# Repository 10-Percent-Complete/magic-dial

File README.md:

# Magic Dial

## Crates for custom PCB
| Name    | Description          | Crate                              |
| ------- | -------------------- | ---------------------------------- |
| HX711   | Strain Gauge IC      | https://crates.io/crates/hx711     |
| GC9A01  | LCD Screen           | https://crates.io/crates/gc9a01-rs |
| MT6701  | Hall Encoder         | https://crates.io/crates/mt6701    |
| TMC6300 | Motor Driver         | N/A                                |
| INA420  | Inline Phase Current | N/A                                |

## Info about devlepment board
| Name                        | URL                                                                         |
| --------------------------- | --------------------------------------------------------------------------- |
| Sparkfun Board              | https://docs.sparkfun.com/SparkFun_IoT_Brushless_Motor_Driver/introduction/ |
| TMC6300 Motor Driver        |                                                                             |
| TMAG5273 Hall Encoder       |                                                                             |
| INA420 Inline Phase Current |                                                                             |
| MCP6021 Low-side Op Amp     |                                                                             |
| WS2812 RGB LED              | https://crates.io/crates/ws2812-spi                                         |

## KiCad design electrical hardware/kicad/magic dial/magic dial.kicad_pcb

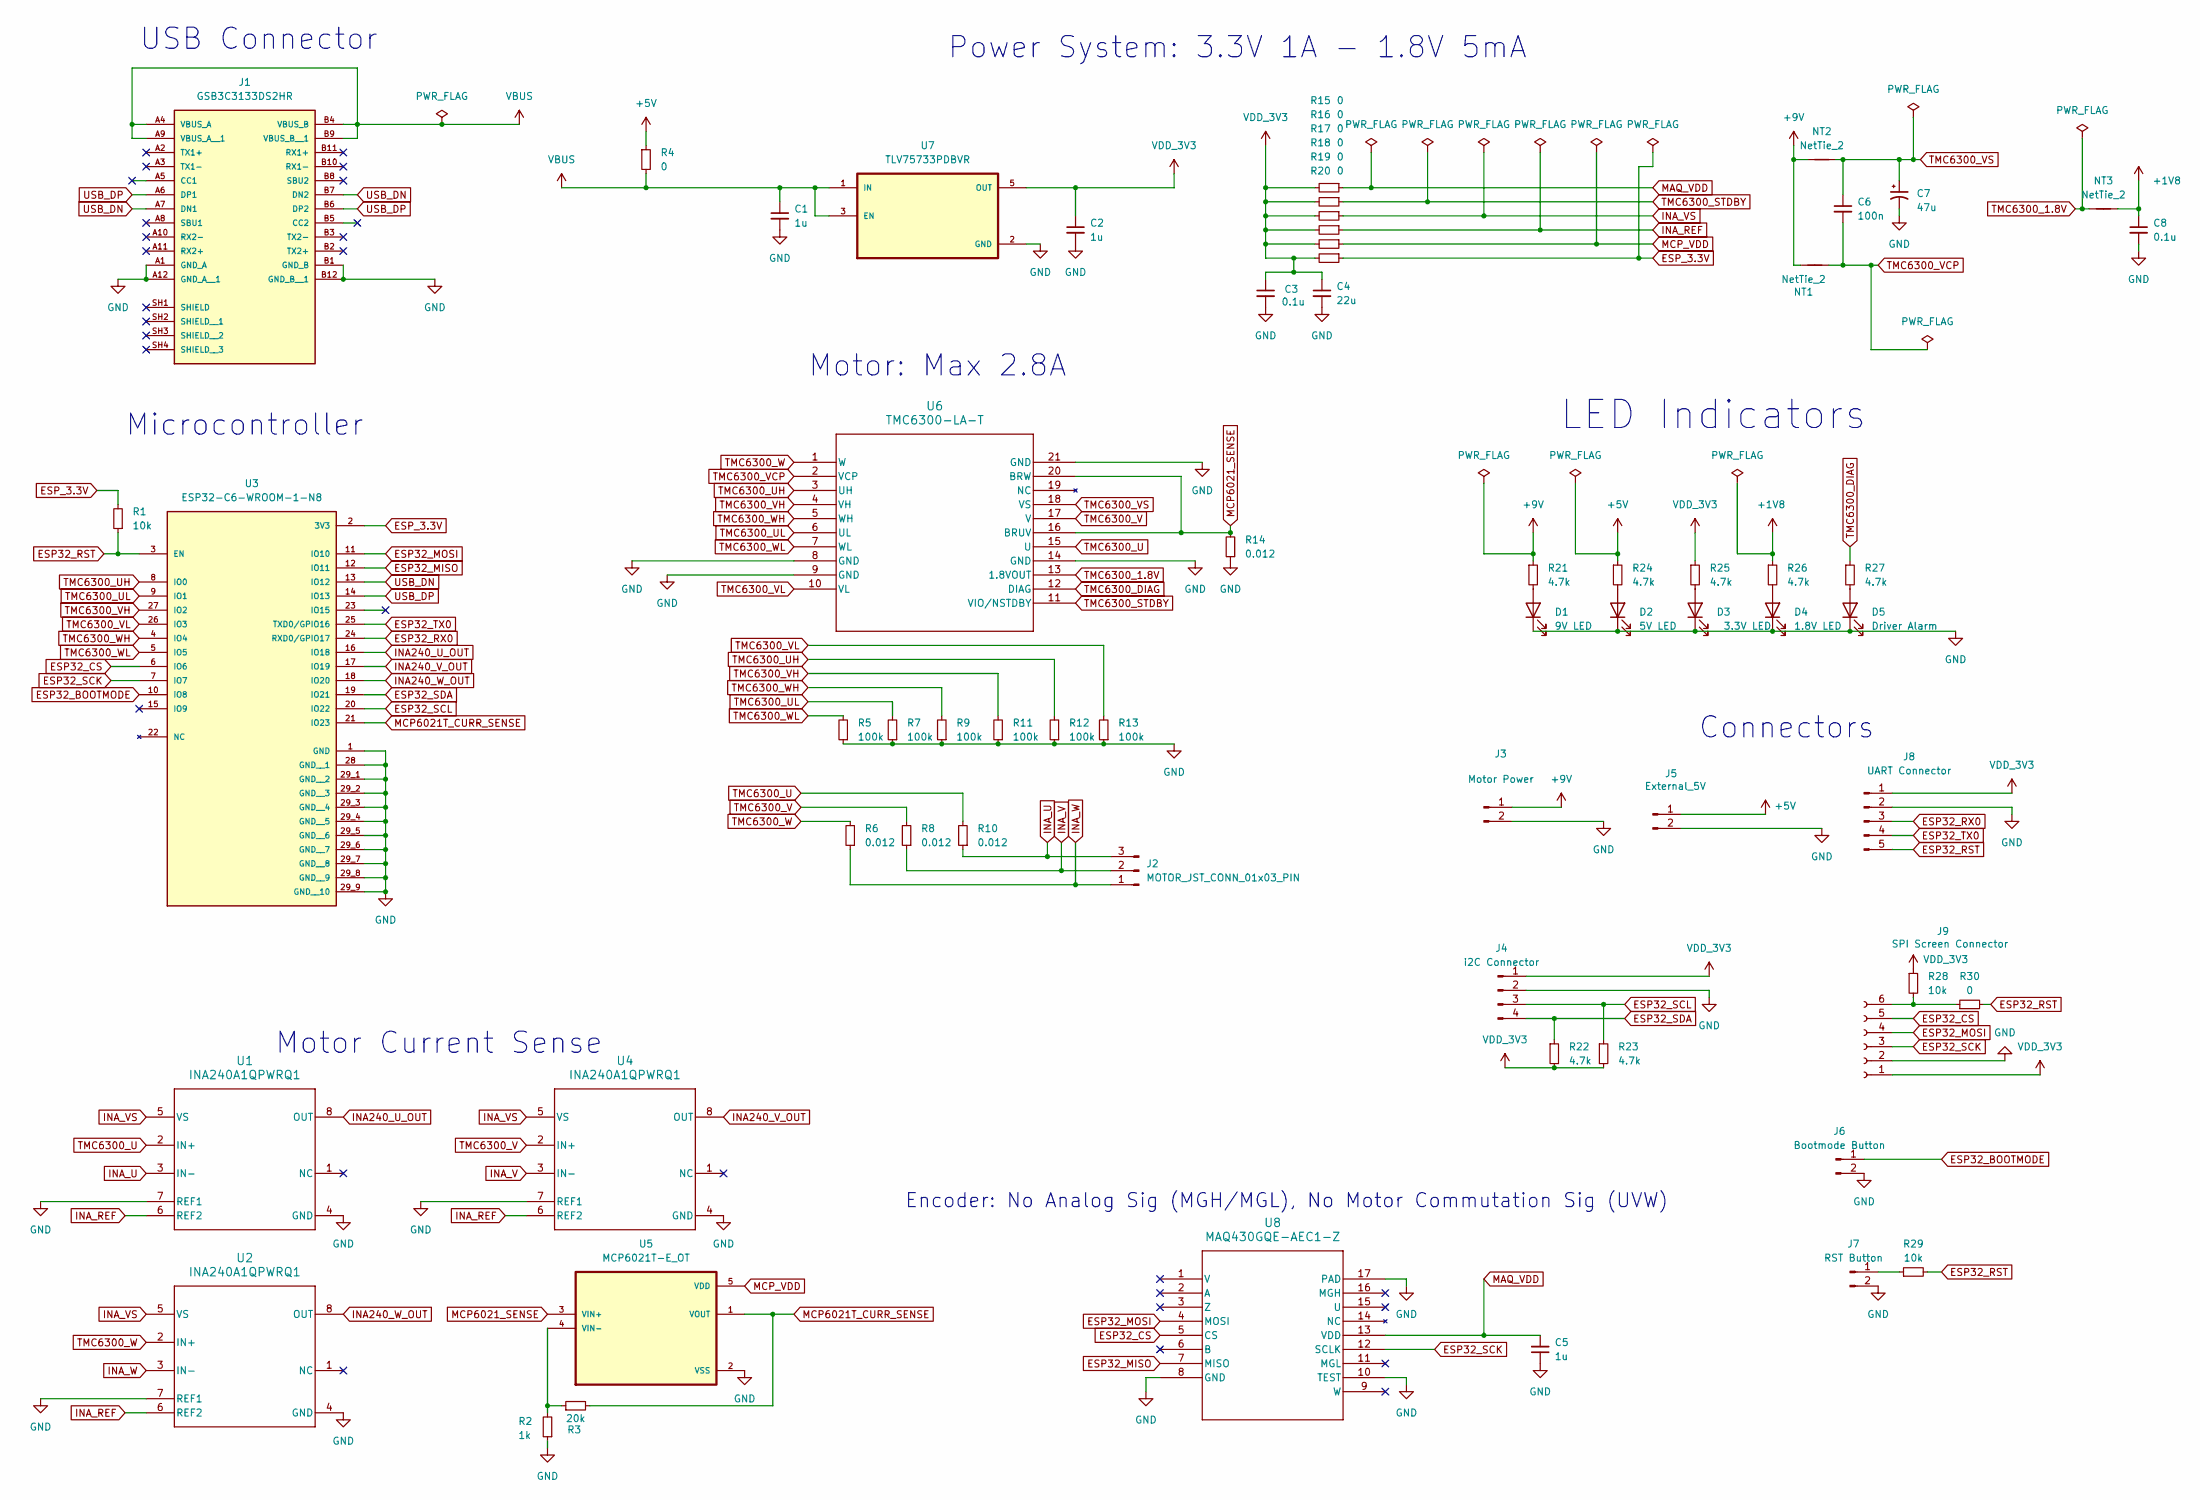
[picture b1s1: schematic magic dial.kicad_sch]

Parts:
C1, C2, C5: 1u; C_1206_3216Metric
C3, C8: 0.1u; C_1206_3216Metric
C4: 22u; C_1206_3216Metric
C6: 100n; C_1206_3216Metric
C7: 47u; C_1206_3216Metric
D1: 9V LED; LED_1206_3216Metric
D2: 5V LED; LED_1206_3216Metric
D3: 3.3V LED; LED_1206_3216Metric
D4: 1.8V LED; LED_1206_3216Metric
D5: Driver Alarm; LED_1206_3216Metric
J1: GSB3C3133DS2HR; AMPHENOL_GSB3C3133DS2HR; PARTREV AX1
J2: MOTOR_JST_CONN_01x03_PIN; JST_GH_SM03B-GHS-TB_1x03-1MP_P1.25mm_Horizontal
J3: Motor Power; PinHeader_1x02_P2.54mm_Vertical
J4: i2C Connector; PinHeader_1x04_P2.54mm_Vertical
J5: External_5V; PinHeader_1x02_P2.54mm_Vertical
J6: Bootmode Button; PinHeader_1x02_P2.54mm_Vertical
J7: RST Button; PinHeader_1x02_P2.54mm_Vertical
J8: UART Connector; PinHeader_1x05_P2.54mm_Vertical
J9: SPI Screen Connector; PinHeader_1x06_P2.54mm_Vertical
NT1, NT2, NT3: NetTie_2; NetTie-2_SMD_Pad0.5mm
R1, R28, R29: 10k; R_1206_3216Metric
R2: 1k; R_1206_3216Metric
R3: 20k; R_1206_3216Metric
R4, R15, R16, R17, R18, R19, R20, R30: 0; R_1206_3216Metric
R5, R7, R9, R11, R12, R13: 100k; R_1206_3216Metric
R6, R8, R10, R14: 0.012; R_1206_3216Metric
R21, R22, R23, R24, R25, R26, R27: 4.7k; R_1206_3216Metric
U1, U2, U4: INA240A1QPWRQ1; PW0008A_M
U3: ESP32-C6-WROOM-1-N8; XCVR_ESP32-C6-WROOM-1-N8; PARTREV 1.0
U5: MCP6021T-E_OT; SOT95P270X145-5N
U6: TMC6300-LA-T; 21-100586_K2033&plus_1C_ADI-M
U7: TLV75733PDBVR; SOT95P280X145-5N
U8: MAQ430GQE-AEC1-Z; QFN-16_MAQ430-M

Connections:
+1V8: C8.1, NT3.2, R26.1
+5V: J5.1, R4.1, R24.1
+9V: J3.1, NT1.1, NT2.1, R21.1
ESP32_BOOTMODE: J6.1, U3.10 (IO8)
ESP32_CS: J9.5, U3.6 (IO6), U8.5 (CS)
ESP32_MISO: U3.12 (IO11), U8.7 (MISO)
ESP32_MOSI: J9.4, U3.11 (IO10), U8.4 (MOSI)
ESP32_RST: J8.5, R1.1, R29.2, R30.2, U3.3 (EN)
ESP32_RX0: J8.3, U3.24 (RXD0/GPIO17)
ESP32_SCK: J9.3, U3.7 (IO7), U8.12 (SCLK)
ESP32_SCL: J4.3, R23.1, U3.20 (IO22)
ESP32_SDA: J4.4, R22.1, U3.19 (IO21)
ESP32_TX0: J8.4, U3.25 (TXD0/GPIO16)
ESP_3.3V: R1.2, R20.1, U3.2 (3V3)
GND: C1.2, C2.2, C3.2, C4.2, C5.1, C7.2, C8.2, D1.1 (K), D2.1 (K), D3.1 (K), D4.1 (K), D5.1 (K), J1.A1 (GND_A), J1.A12 (GND_A__1), J1.B1 (GND_B), J1.B12 (GND_B__1), J3.2, J4.2, J5.2, J6.2, J7.2, J8.2, J9.2, R2.1, R5.1, R7.1, R9.1, R11.1, R12.1, R13.1, R14.1, U1.4 (GND), U1.7 (REF1), U2.4 (GND), U2.7 (REF1), U3.1 (GND), U3.28 (GND__1), U3.29_1 (GND__2), U3.29_2 (GND__3), U3.29_3 (GND__4), U3.29_4 (GND__5), U3.29_5 (GND__6), U3.29_6 (GND__7), U3.29_7 (GND__8), U3.29_8 (GND__9), U3.29_9 (GND__10), U4.4 (GND), U4.7 (REF1), U5.2 (VSS), U6.8 (GND), U6.9 (GND), U6.14 (GND), U6.21 (GND), U7.2 (GND), U8.8 (GND), U8.10 (TEST), U8.17 (PAD)
INA240_U_OUT: U1.8 (OUT), U3.16 (IO18)
INA240_V_OUT: U3.17 (IO19), U4.8 (OUT)
INA240_W_OUT: U2.8 (OUT), U3.18 (IO20)
INA_REF: R18.1, U1.6 (REF2), U2.6 (REF2), U4.6 (REF2)
INA_U: J2.3, R10.1, U1.3 (IN-)
INA_V: J2.2, R8.1, U4.3 (IN-)
INA_VS: R17.1, U1.5 (VS), U2.5 (VS), U4.5 (VS)
INA_W: J2.1, R6.1, U2.3 (IN-)
MAQ_VDD: C5.2, R15.1, U8.13 (VDD)
MCP6021T_CURR_SENSE: R3.2, U3.21 (IO23), U5.1 (VOUT)
MCP6021_SENSE: R14.2, U5.3 (VIN+), U6.16 (BRUV), U6.20 (BRW)
MCP_VDD: R19.1, U5.5 (VDD)
unnamed: D1.2 (A), R21.2
unnamed: D2.2 (A), R24.2
unnamed: D3.2 (A), R25.2
unnamed: D4.2 (A), R26.2
unnamed: D5.2 (A), R27.2
unnamed: J7.1, R29.1
unnamed: J9.6, R28.2, R30.1
unnamed: R2.2, R3.1, U5.4 (VIN-)
TMC6300_1.8V: NT3.1, U6.13 (1.8VOUT)
TMC6300_DIAG: R27.1, U6.12 (DIAG)
TMC6300_STDBY: R16.1, U6.11 (VIO/NSTDBY)
TMC6300_U: R10.2, U1.2 (IN+), U6.15 (U)
TMC6300_UH: R12.2, U3.8 (IO0), U6.3 (UH)
TMC6300_UL: R7.2, U3.9 (IO1), U6.6 (UL)
TMC6300_V: R8.2, U4.2 (IN+), U6.17 (V)
TMC6300_VCP: C6.2, NT1.2, U6.2 (VCP)
TMC6300_VH: R11.2, U3.27 (IO2), U6.4 (VH)
TMC6300_VL: R13.2, U3.26 (IO3), U6.10 (VL)
TMC6300_VS: C6.1, C7.1, NT2.2, U6.18 (VS)
TMC6300_W: R6.2, U2.2 (IN+), U6.1 (W)
TMC6300_WH: R9.2, U3.4 (IO4), U6.5 (WH)
TMC6300_WL: R5.2, U3.5 (IO5), U6.7 (WL)
USB_DN: J1.A7 (DN1), J1.B7 (DN2), U3.13 (IO12)
USB_DP: J1.A6 (DP1), J1.B6 (DP2), U3.14 (IO13)
VBUS: C1.1, J1.A4 (VBUS_A), J1.A9 (VBUS_A__1), J1.B4 (VBUS_B), J1.B9 (VBUS_B__1), R4.2, U7.1 (IN), U7.3 (EN)
VDD_3V3: C2.1, C3.1, C4.1, J4.1, J8.1, J9.1, R15.2, R16.2, R17.2, R18.2, R19.2, R20.2, R22.2, R23.2, R25.1, R28.1, U7.5 (OUT)

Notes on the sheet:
Microcontroller
Motor: Max 2.8A
Connectors
USB Connector
Motor Current Sense
LED Indicators
Power System: 3.3V 1A - 1.8V 5mA
Encoder: No Analog Sig (MGH/MGL), No Motor Commutation Sig (UVW)

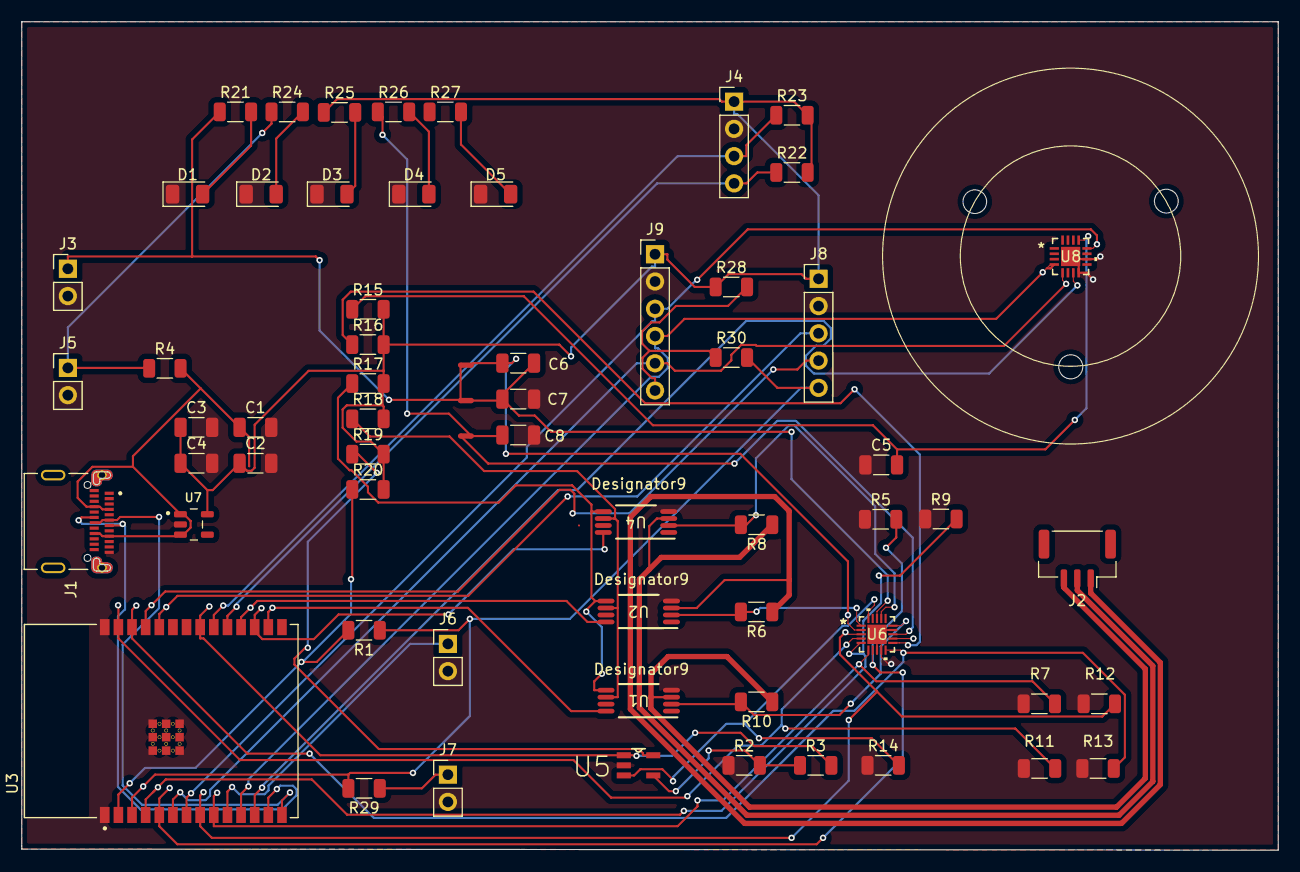
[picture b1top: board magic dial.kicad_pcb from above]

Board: 2 copper layers, 117.1 x 77.2 mm, 63 parts (0 on the bottom side), 53 nets.

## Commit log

2025-01-14 Day 1
    Day 1
    Test Firmware and Reference material
2025-01-14 Added Encoder Code
    Added Encoder Code
2025-01-16 Created Rust blink rgb led for sparkfun board
2025-02-02 Major KiCad Update and EDA Models
    Major KiCad Update and EDA Models
2025-02-03 Added proof of concept rust code for reading hall effect axis registers
2025-02-03 Major Update: Added Power, and Motor to Schematics
    Major Update: Added Power, and Motor to Schematics
2025-02-06 Updated readme format
2025-02-06 Created file structure for rust sensor drivers
2025-02-09 Setup driver structure for tmag encoder
2025-02-09 Added configure/read functions for magnetic sensor
2025-02-10 Added conversion to angle read function to return in degrees and 4 decimal values
2025-02-13 Added current sensor adc reading support
2025-02-18 Added open loop commutation control and added all configuration functions for tmag driver
2025-03-08 Organized file hiearchy through control/motor/pwm.rs modules. Hard coded 120 trapezoid open velocity
2025-03-20 PWM motor commutation setup
2025-04-14 Completed V1 Schematics, requires validation.
    Completed V1 Schematics, requires validation.
2025-04-14 Completed Validation or Schematic. Removed Errors. Needs Footprint assignment
2025-04-14 Assigned footprints for universal components. Need to do custom Components
    Assigned footprints for universal components. Need to do custom Components
2025-04-14 Completed Initial Layout for PCB
2025-04-14 Added space vector foc equations based on position sector
2025-04-14 Auto Route Progress: Incomplete.
    Auto Route Progress: Incomplete.
